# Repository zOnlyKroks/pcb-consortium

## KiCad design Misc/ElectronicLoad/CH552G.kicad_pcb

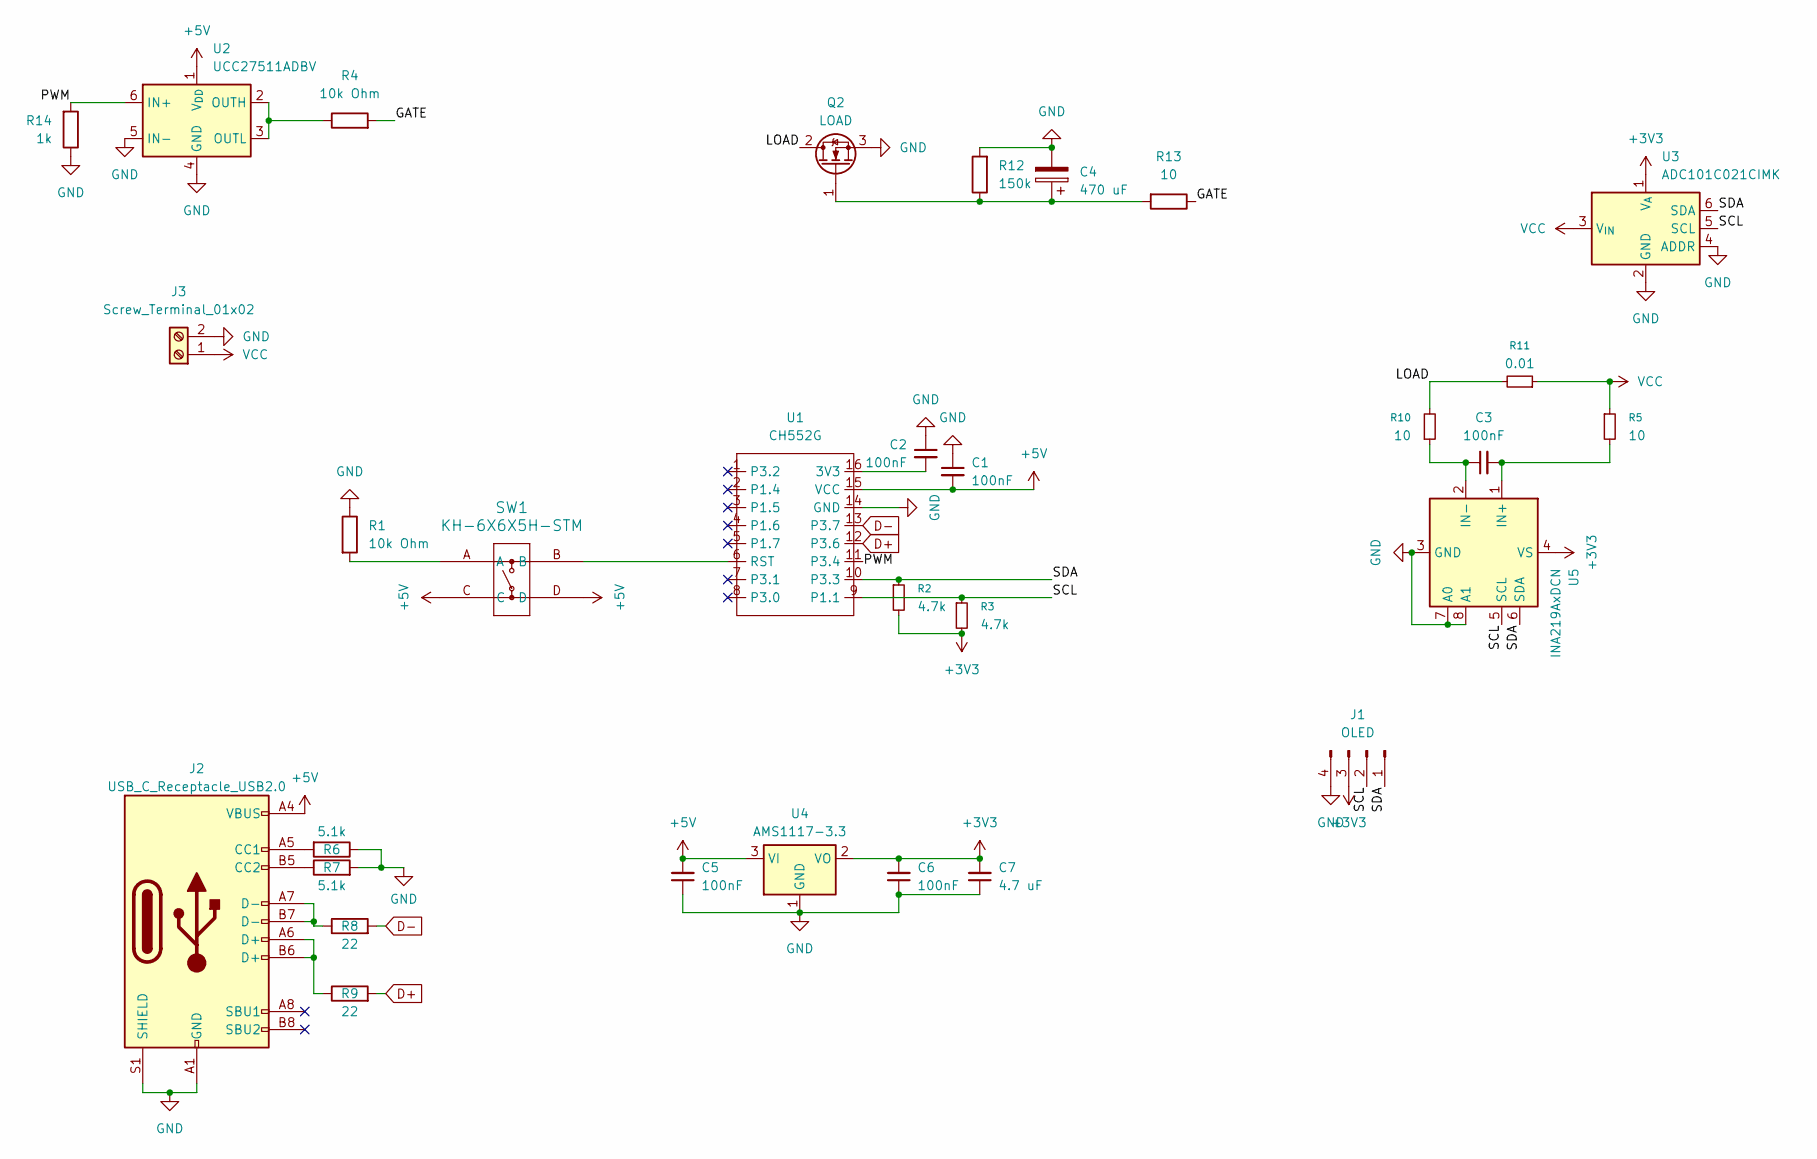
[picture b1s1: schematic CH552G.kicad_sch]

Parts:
C1, C2, C3, C5, C6: 100nF; C_0805_2012Metric; LCSC Part # C49678
C4: 470 uF
C7: 4.7 uF; C_0805_2012Metric; LCSC Part # C49678
J1: OLED; PinHeader_1x04_P2.54mm_Vertical
J2: USB_C_Receptacle_USB2.0; USB_C_Receptacle_HRO_TYPE-C-31-M-12; JlcRotOffset 180
J3: Screw_Terminal_01x02; WJ500V-5.08-2P
Q2: LOAD; TO-220-3_Vertical
R1, R4: 10k Ohm; R_0805_2012Metric; LCSC Part # C17414
R2, R3: 4.7k; R_0805_2012Metric
R5, R10: 10; R_0805_2012Metric
R6, R7: 5.1k; R_0805_2012Metric; LCSC Part # C23186
R8, R9: 22; R_0805_2012Metric; LCSC Part # C23345
R11: 0.01; R_0805_2012Metric
R12: 150k; R_0805_2012Metric; LCSC Part # C17414
R13: 10; R_0805_2012Metric; LCSC Part # C17414
R14: 1k; R_0805_2012Metric; LCSC Part # C17414
SW1: KH-6X6X5H-STM; KH-6X6X5H-STM_SKE; LCSC Part # C2837531
U1: CH552G; LCSC Part # C111292
U2: UCC27511ADBV; SOT-23-6
U3: ADC101C021CIMK; SOT-23-6
U4: AMS1117-3.3; SOT-223-3_TabPin2
U5: INA219AxDCN; SOT-23-8

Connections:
+3V3: C6.2, C7.2, J1.3, R2.2, R3.2, U3.1 (V_{A}), U4.2 (VO), U5.4 (VS)
+5V: C1.2, C5.2, J2.A4 (VBUS), J2.A9 (VBUS), J2.B4 (VBUS), J2.B9 (VBUS), SW1.C, SW1.D, U1.15 (VCC), U2.1 (V_{DD}), U4.3 (VI)
/GATE: R4.2, R13.1
/LOAD: Q2.2 (D), R10.2, R11.2
/PWM: R14.2, U1.11 (P3.4), U2.6 (IN+)
/SCL: J1.2, R3.1, U1.9 (P1.1), U3.5 (SCL), U5.5 (SCL)
/SDA: J1.1, R2.1, U1.10 (P3.3), U3.6 (SDA), U5.6 (SDA)
D+: R9.2, U1.12 (P3.6)
D-: R8.2, U1.13 (P3.7)
GND: C1.1, C2.1, C4.2, C5.1, C6.1, C7.1, J1.4, J2.A1 (GND), J2.A12 (GND), J2.B1 (GND), J2.B12 (GND), J2.S1 (SHIELD), J3.2, Q2.3 (S), R1.1, R6.1, R7.2, R12.2, R14.1, U1.14 (GND), U2.4 (GND), U2.5 (IN-), U3.2 (GND), U3.4 (ADDR), U4.1 (GND), U5.3 (GND), U5.7 (A0), U5.8 (A1)
unnamed: J2.A5 (CC1), R6.2
unnamed: J2.B5 (CC2), R7.1
unnamed: J2.A6 (D+), J2.B6 (D+), R9.1
unnamed: J2.A7 (D-), J2.B7 (D-), R8.1
unnamed: C4.1, Q2.1 (G), R12.1, R13.2
unnamed: R1.2, SW1.A
unnamed: C2.2, U1.16 (3V3)
unnamed: SW1.B, U1.6 (RST)
unnamed: R4.1, U2.2 (OUTH), U2.3 (OUTL)
unnamed: C3.2, R5.2, U5.1 (IN+)
unnamed: C3.1, R10.1, U5.2 (IN-)
VCC: J3.1, R5.1, R11.1, U3.3 (V_{IN})

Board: 2 copper layers, 31 parts (0 on the bottom side), 22 nets, no tracks yet.

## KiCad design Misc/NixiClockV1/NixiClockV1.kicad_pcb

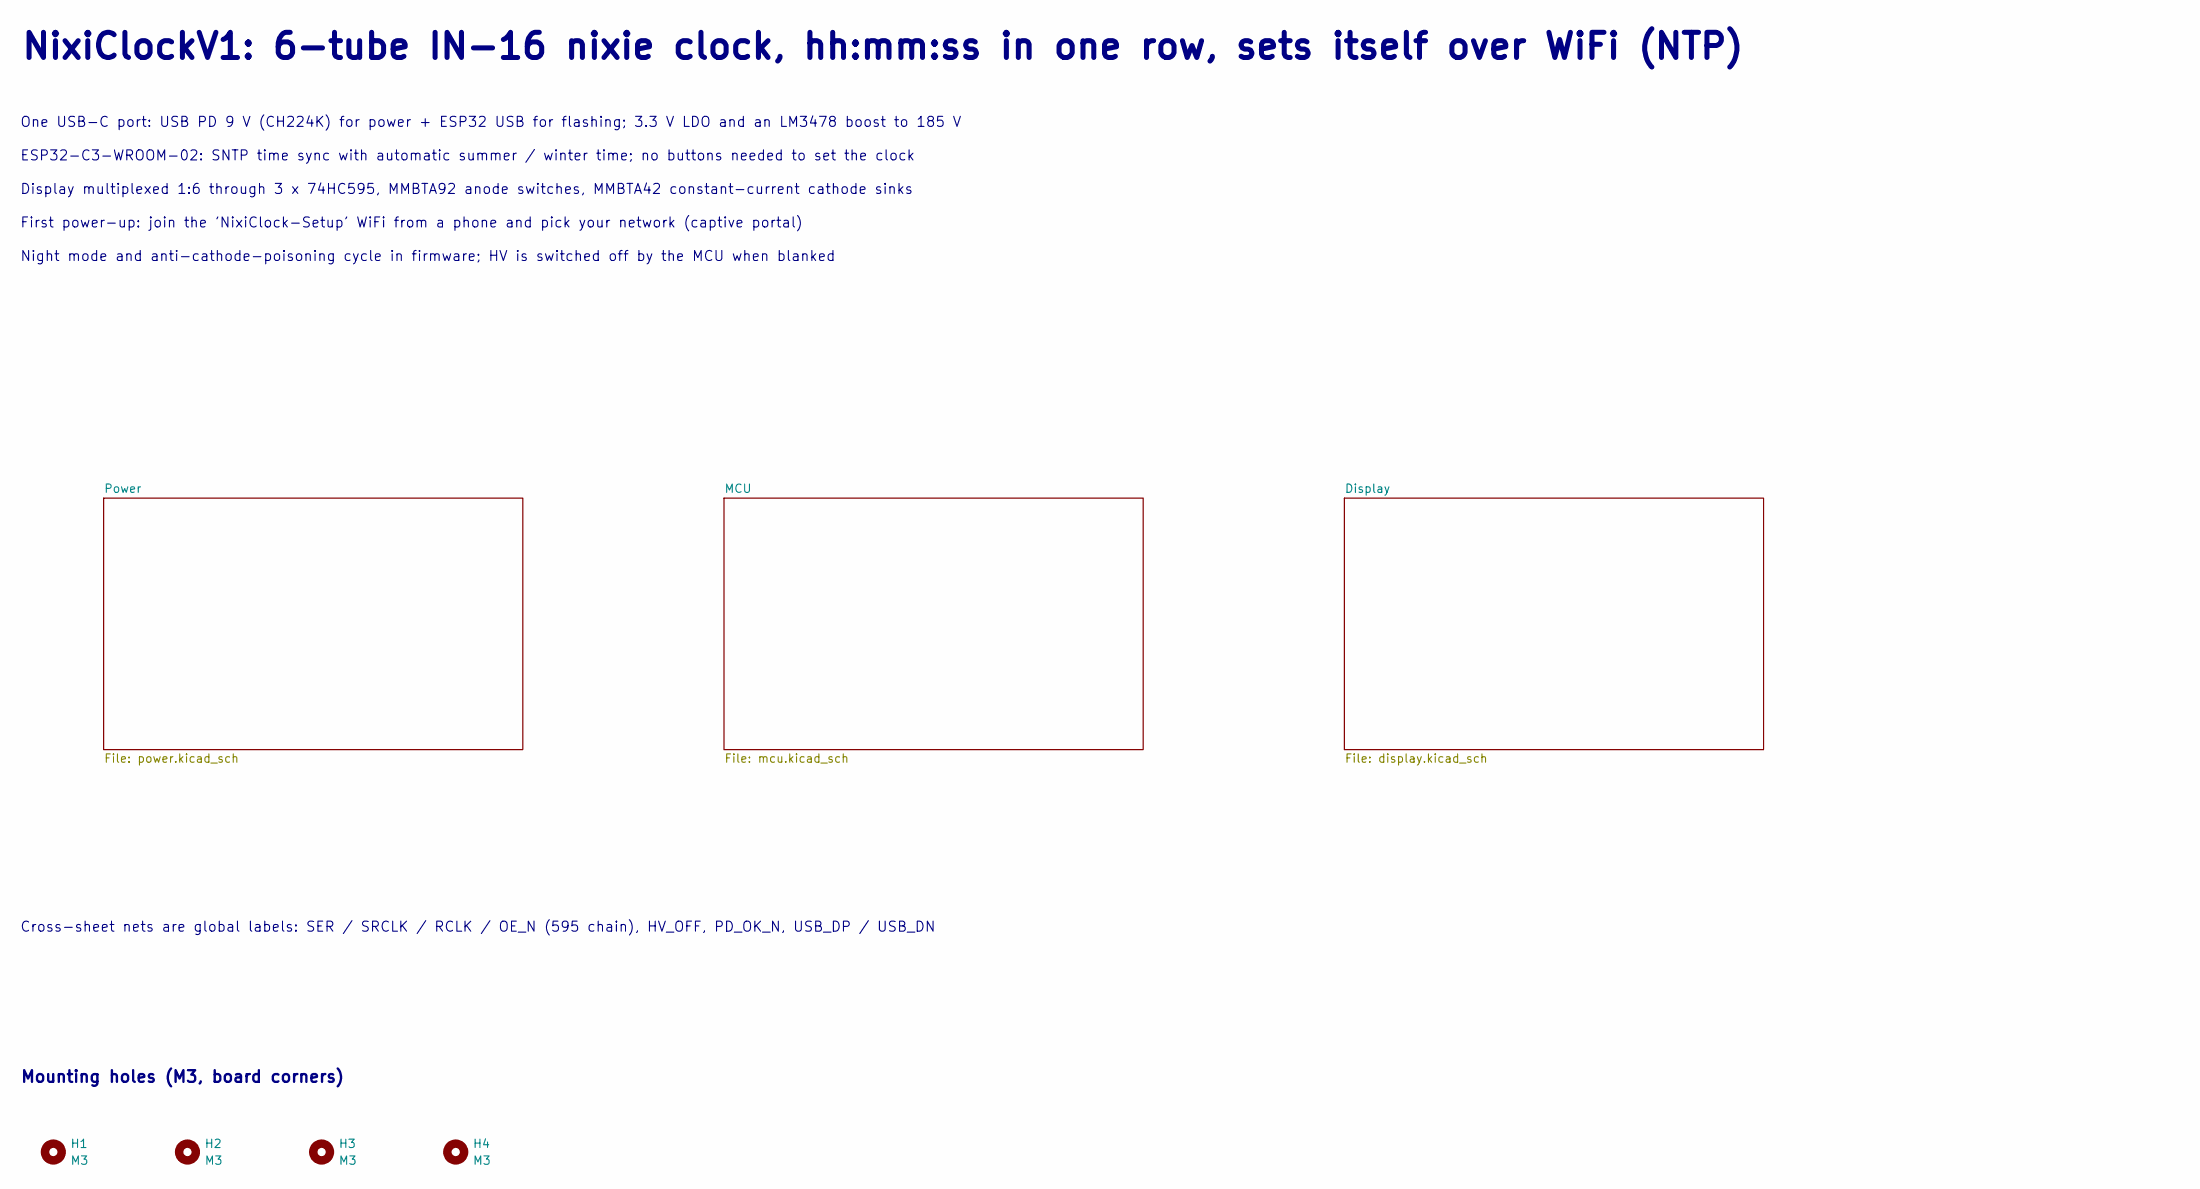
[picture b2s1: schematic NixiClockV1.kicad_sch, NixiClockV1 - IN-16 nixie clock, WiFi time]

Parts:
H1, H2, H3, H4: M3; MountingHole_3.2mm_M3

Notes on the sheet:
Night mode and anti-cathode-poisoning cycle in firmware; HV is switched off by the MCU when blanked
Mounting holes (M3, board corners)
Display multiplexed 1:6 through 3 x 74HC595, MMBTA92 anode switches, MMBTA42 constant-current cathode sinks
Cross-sheet nets are global labels: SER / SRCLK / RCLK / OE_N (595 chain), HV_OFF, PD_OK_N, USB_DP / USB_DN
One USB-C port: USB PD 9 V (CH224K) for power + ESP32 USB for flashing; 3.3 V LDO and an LM3478 boost to 185 V
First power-up: join the 'NixiClock-Setup' WiFi from a phone and pick your network (captive portal)
ESP32-C3-WROOM-02: SNTP time sync with automatic summer / winter time; no buttons needed to set the clock
NixiClockV1: 6-tube IN-16 nixie clock, hh:mm:ss in one row, sets itself over WiFi (NTP)

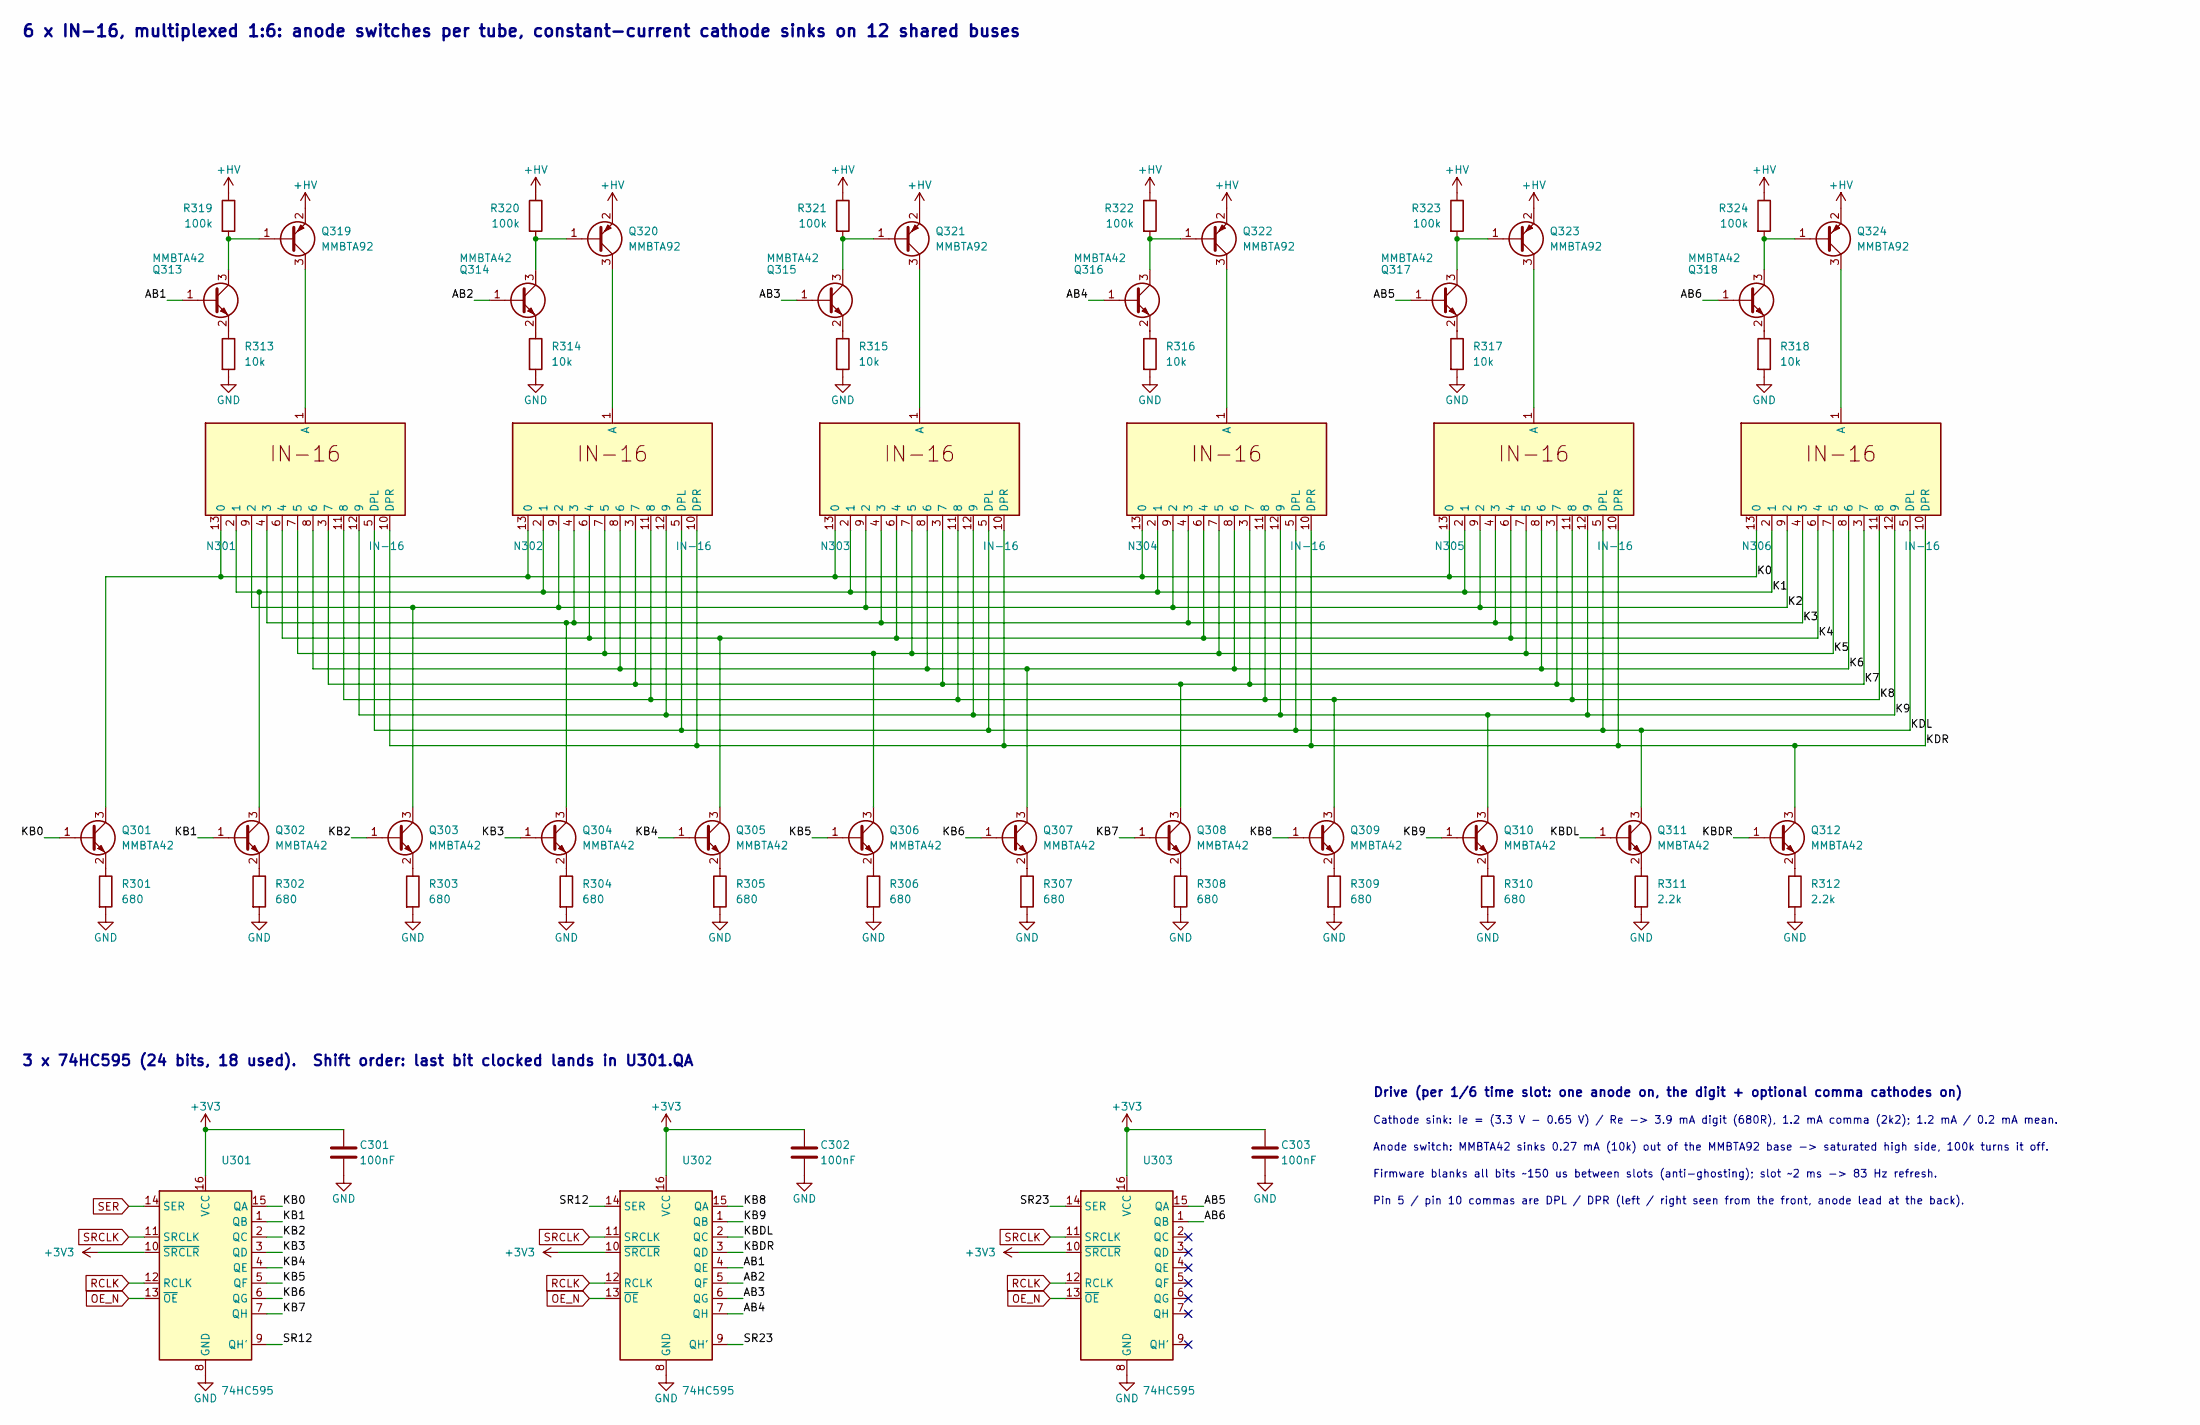
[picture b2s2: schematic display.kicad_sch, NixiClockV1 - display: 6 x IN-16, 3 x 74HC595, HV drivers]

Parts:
C301, C302, C303: 100nF; C_0603_1608Metric; LCSC Part # C14663
N301, N302, N303, N304, N305, N306: IN-16
Q301, Q302, Q303, Q304, Q305, Q306, Q307, Q308, Q309, Q310, Q311, Q312, Q313, Q314, Q315, Q316, Q317, Q318: MMBTA42; SOT-23; LCSC Part # C20069138
Q319, Q320, Q321, Q322, Q323, Q324: MMBTA92; SOT-23; LCSC Part # C20069146
R301, R302, R303, R304, R305, R306, R307, R308, R309, R310: 680; R_0603_1608Metric; LCSC Part # C23228
R311, R312: 2.2k; R_0603_1608Metric; LCSC Part # C4190
R313, R314, R315, R316, R317, R318: 10k; R_0603_1608Metric; LCSC Part # C25804
R319, R320, R321, R322, R323, R324: 100k; R_0603_1608Metric; LCSC Part # C25803
U301, U302, U303: 74HC595; SOIC-16_3.9x9.9mm_P1.27mm; LCSC Part # C20612517

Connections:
+3V3: C301.1, C302.1, C303.1, U301.10 (~SRCLR), U301.16 (VCC), U302.10 (~SRCLR), U302.16 (VCC), U303.10 (~SRCLR), U303.16 (VCC); also elsewhere on the board
+HV: Q319.2 (E), Q320.2 (E), Q321.2 (E), Q322.2 (E), Q323.2 (E), Q324.2 (E), R319.1, R320.1, R321.1, R322.1, R323.1, R324.1; also elsewhere on the board
/Display/AB1: Q313.1 (B), U302.4 (QE)
/Display/AB2: Q314.1 (B), U302.5 (QF)
/Display/AB3: Q315.1 (B), U302.6 (QG)
/Display/AB4: Q316.1 (B), U302.7 (QH)
/Display/AB5: Q317.1 (B), U303.15 (QA)
/Display/AB6: Q318.1 (B), U303.1 (QB)
/Display/K0: N301.13 (0), N302.13 (0), N303.13 (0), N304.13 (0), N305.13 (0), N306.13 (0), Q301.3 (C)
/Display/K1: N301.2 (1), N302.2 (1), N303.2 (1), N304.2 (1), N305.2 (1), N306.2 (1), Q302.3 (C)
/Display/K2: N301.9 (2), N302.9 (2), N303.9 (2), N304.9 (2), N305.9 (2), N306.9 (2), Q303.3 (C)
/Display/K3: N301.4 (3), N302.4 (3), N303.4 (3), N304.4 (3), N305.4 (3), N306.4 (3), Q304.3 (C)
/Display/K4: N301.6 (4), N302.6 (4), N303.6 (4), N304.6 (4), N305.6 (4), N306.6 (4), Q305.3 (C)
/Display/K5: N301.7 (5), N302.7 (5), N303.7 (5), N304.7 (5), N305.7 (5), N306.7 (5), Q306.3 (C)
/Display/K6: N301.8 (6), N302.8 (6), N303.8 (6), N304.8 (6), N305.8 (6), N306.8 (6), Q307.3 (C)
/Display/K7: N301.3 (7), N302.3 (7), N303.3 (7), N304.3 (7), N305.3 (7), N306.3 (7), Q308.3 (C)
/Display/K8: N301.11 (8), N302.11 (8), N303.11 (8), N304.11 (8), N305.11 (8), N306.11 (8), Q309.3 (C)
/Display/K9: N301.12 (9), N302.12 (9), N303.12 (9), N304.12 (9), N305.12 (9), N306.12 (9), Q310.3 (C)
/Display/KB0: Q301.1 (B), U301.15 (QA)
/Display/KB1: Q302.1 (B), U301.1 (QB)
/Display/KB2: Q303.1 (B), U301.2 (QC)
/Display/KB3: Q304.1 (B), U301.3 (QD)
/Display/KB4: Q305.1 (B), U301.4 (QE)
/Display/KB5: Q306.1 (B), U301.5 (QF)
/Display/KB6: Q307.1 (B), U301.6 (QG)
/Display/KB7: Q308.1 (B), U301.7 (QH)
/Display/KB8: Q309.1 (B), U302.15 (QA)
/Display/KB9: Q310.1 (B), U302.1 (QB)
/Display/KBDL: Q311.1 (B), U302.2 (QC)
/Display/KBDR: Q312.1 (B), U302.3 (QD)
/Display/KDL: N301.5 (DPL), N302.5 (DPL), N303.5 (DPL), N304.5 (DPL), N305.5 (DPL), N306.5 (DPL), Q311.3 (C)
/Display/KDR: N301.10 (DPR), N302.10 (DPR), N303.10 (DPR), N304.10 (DPR), N305.10 (DPR), N306.10 (DPR), Q312.3 (C)
/Display/SR12: U301.9 (QH'), U302.14 (SER)
/Display/SR23: U302.9 (QH'), U303.14 (SER)
GND: C301.2, C302.2, C303.2, R301.2, R302.2, R303.2, R304.2, R305.2, R306.2, R307.2, R308.2, R309.2, R310.2, R311.2, R312.2, R313.2, R314.2, R315.2, R316.2, R317.2, R318.2, U301.8 (GND), U302.8 (GND), U303.8 (GND); also elsewhere on the board
unnamed: N301.1 (A), Q319.3 (C)
unnamed: N302.1 (A), Q320.3 (C)
unnamed: N303.1 (A), Q321.3 (C)
unnamed: N304.1 (A), Q322.3 (C)
unnamed: N305.1 (A), Q323.3 (C)
unnamed: N306.1 (A), Q324.3 (C)
unnamed: Q301.2 (E), R301.1
unnamed: Q302.2 (E), R302.1
unnamed: Q303.2 (E), R303.1
unnamed: Q304.2 (E), R304.1
unnamed: Q305.2 (E), R305.1
unnamed: Q306.2 (E), R306.1
unnamed: Q307.2 (E), R307.1
unnamed: Q308.2 (E), R308.1
unnamed: Q309.2 (E), R309.1
unnamed: Q310.2 (E), R310.1
unnamed: Q311.2 (E), R311.1
unnamed: Q312.2 (E), R312.1
unnamed: Q313.3 (C), Q319.1 (B), R319.2
unnamed: Q313.2 (E), R313.1
unnamed: Q314.3 (C), Q320.1 (B), R320.2
unnamed: Q314.2 (E), R314.1
unnamed: Q315.3 (C), Q321.1 (B), R321.2
unnamed: Q315.2 (E), R315.1
unnamed: Q316.3 (C), Q322.1 (B), R322.2
unnamed: Q316.2 (E), R316.1
unnamed: Q317.3 (C), Q323.1 (B), R323.2
unnamed: Q317.2 (E), R317.1
unnamed: Q318.3 (C), Q324.1 (B), R324.2
unnamed: Q318.2 (E), R318.1
OE_N: U301.13 (~OE), U302.13 (~OE), U303.13 (~OE); also elsewhere on the board
RCLK: U301.12 (RCLK), U302.12 (RCLK), U303.12 (RCLK); also elsewhere on the board
SER: U301.14 (SER); also elsewhere on the board
SRCLK: U301.11 (SRCLK), U302.11 (SRCLK), U303.11 (SRCLK); also elsewhere on the board

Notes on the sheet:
3 x 74HC595 (24 bits, 18 used). Shift order: last bit clocked lands in U301.QA
Drive (per 1/6 time slot: one anode on, the digit + optional comma cathodes on)
Pin 5 / pin 10 commas are DPL / DPR (left / right seen from the front, anode lead at the back).
6 x IN-16, multiplexed 1:6: anode switches per tube, constant-current cathode sinks on 12 shared buses
Firmware blanks all bits ~150 us between slots (anti-ghosting); slot ~2 ms -> 83 Hz refresh.
Anode switch: MMBTA42 sinks 0.27 mA (10k) out of the MMBTA92 base -> saturated high side, 100k turns it off.
Cathode sink: Ie = (3.3 V - 0.65 V) / Re -> 3.9 mA digit (680R), 1.2 mA comma (2k2); 1.2 mA / 0.2 mA mean.

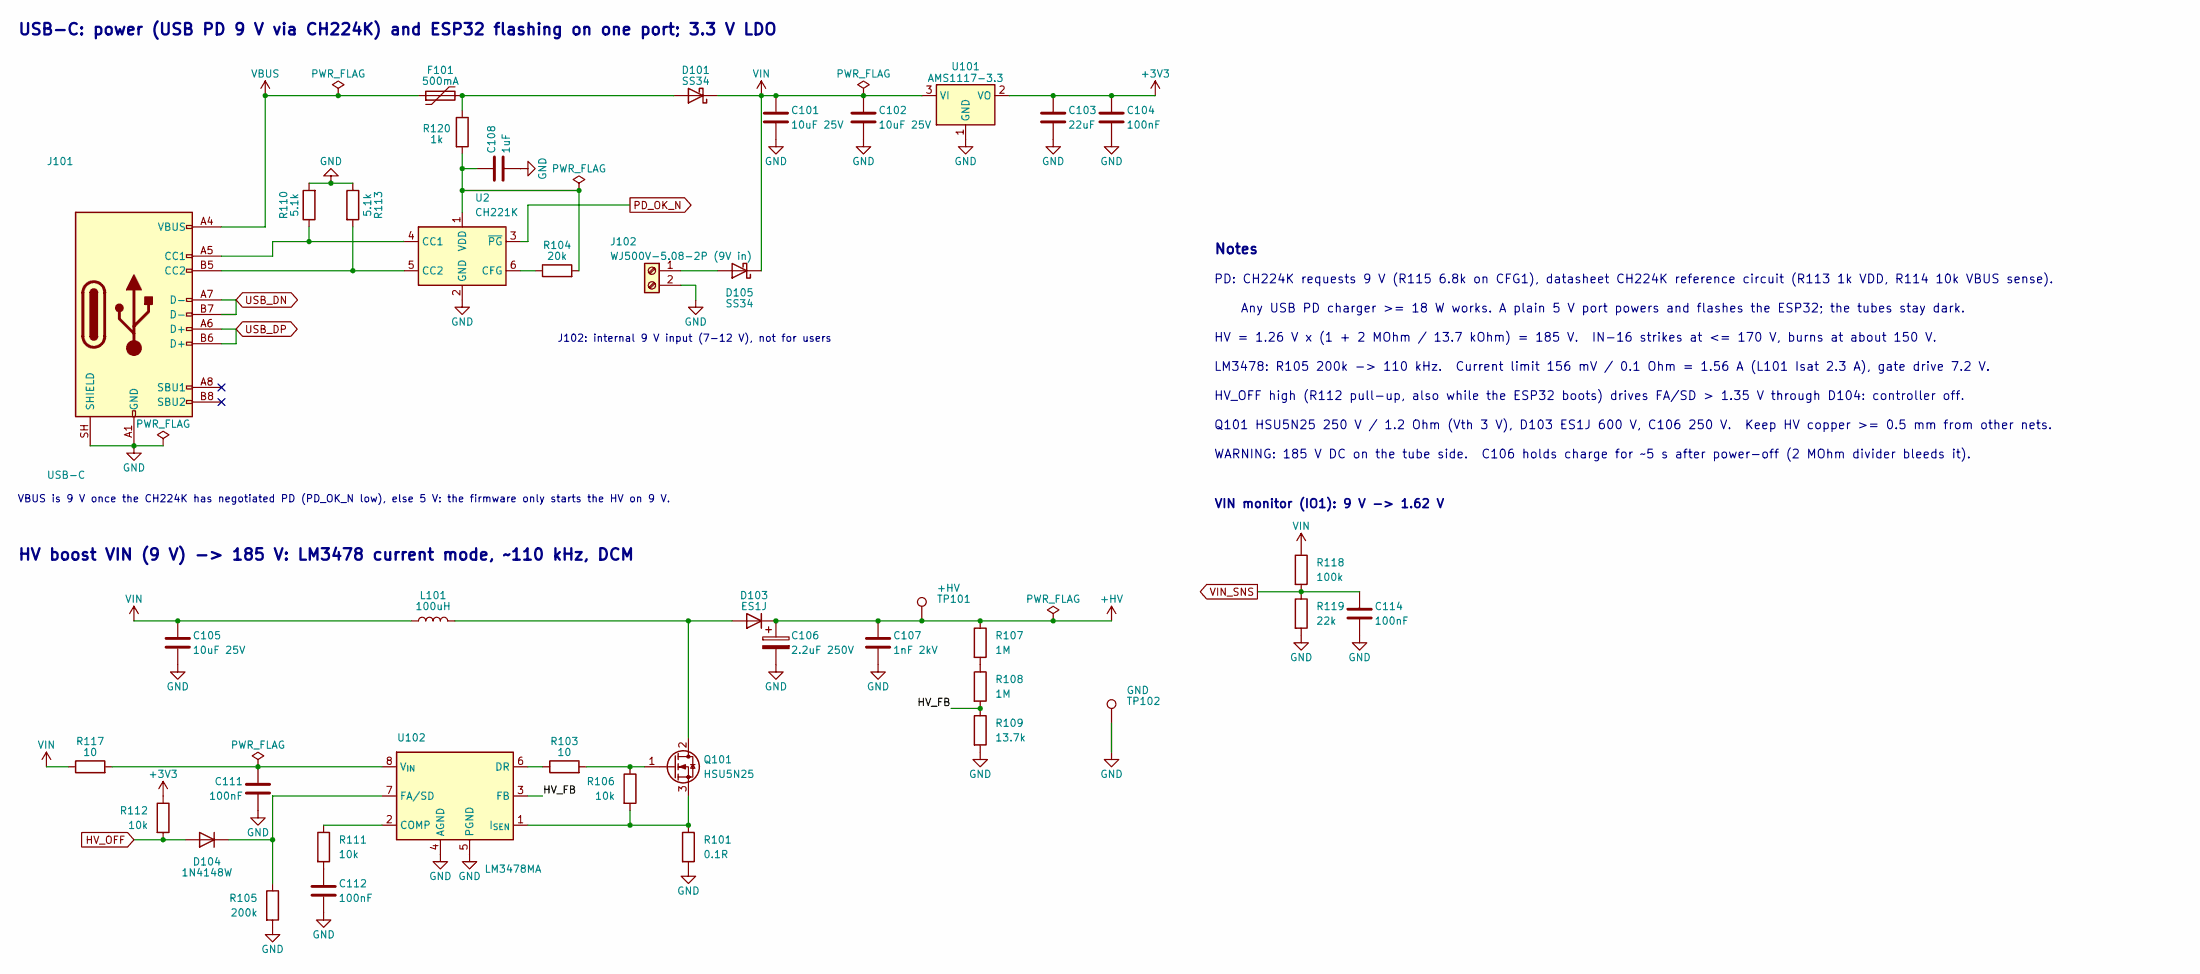
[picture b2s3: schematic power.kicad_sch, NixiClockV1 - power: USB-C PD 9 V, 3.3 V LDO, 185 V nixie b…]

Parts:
C101, C102, C105: 10uF 25V; C_0805_2012Metric; LCSC Part # C15850
C103: 22uF; C_0805_2012Metric; LCSC Part # C45783
C104, C111, C112, C114: 100nF; C_0603_1608Metric; LCSC Part # C14663
C106: 2.2uF 250V; CP_Elec_6.3x9.9; LCSC Part # C22387991
C107: 1nF 2kV; C_1206_3216Metric; LCSC Part # C9196
C108: 1uF; C_0603_1608Metric; LCSC Part # C15849
D101, D105: SS34; D_SMA; LCSC Part # C8678
D103: ES1J; D_SMA; LCSC Part # C18199159
D104: 1N4148W; D_SOD-123; LCSC Part # C81598
F101: 500mA; Fuse_1206_3216Metric; LCSC Part # C135341
J101: USB-C; USB_C_Receptacle_HRO_TYPE-C-31-M-12; LCSC Part # C165948
J102: WJ500V-5.08-2P (9V in); TerminalBlock_Phoenix_MKDS-1,5-2-5.08_1x02_P5.08mm_Horizont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; LCSC Part # C8465
L101: 100uH; L_APV_APH1040; LCSC Part # C19634020
Q101: HSU5N25; TO-252-2; LCSC Part # C22359255
R101: 0.1R; R_1206_3216Metric; LCSC Part # C25334
R103, R117: 10; R_0603_1608Metric; LCSC Part # C22859
R104: 20k; R_0603_1608Metric; LCSC Part # C4184
R105: 200k; R_0603_1608Metric; LCSC Part # C25811
R106, R111, R112: 10k; R_0603_1608Metric; LCSC Part # C25804
R107, R108: 1M; R_1206_3216Metric; LCSC Part # C17927
R109: 13.7k; R_0603_1608Metric; LCSC Part # C407628
R110, R113: 5.1k; R_0603_1608Metric; LCSC Part # C23186
R118: 100k; R_0603_1608Metric; LCSC Part # C25803
R119: 22k; R_0603_1608Metric; LCSC Part # C31850
R120: 1k; R_0603_1608Metric; LCSC Part # C21190
TP101: +HV; TestPoint_Pad_D1.5mm
TP102: GND; TestPoint_Pad_D1.5mm
U2: CH221K; SOT-23-6; LCSC Part # C5125736
U101: AMS1117-3.3; SOT-223-3_TabPin2; LCSC Part # C6186
U102: LM3478MA; SOIC-8_3.9x4.9mm_P1.27mm; LCSC Part # C115907

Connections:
+3V3: C103.1, C104.1, R112.1, U101.2 (VO); also elsewhere on the board
+HV: C106.1, C107.1, D103.1 (K), R107.1, TP101.1 (1_1); also elsewhere on the board
/Power/HV_FB: R108.2, R109.1, U102.3 (FB)
GND: C101.2, C102.2, C103.2, C104.2, C105.2, C106.2, C107.2, C108.2, C111.2, C112.2, C114.2, J101.A1 (GND), J101.A12 (GND), J101.B1 (GND), J101.B12 (GND), J101.SH (SHIELD), J102.2, R101.2, R105.2, R109.2, R110.2, R113.1, R119.2, TP102.1 (1_1), U2.2 (GND), U101.1 (GND), U102.4 (AGND), U102.5 (PGND); also elsewhere on the board
HV_OFF: D104.2 (A), R112.2; also elsewhere on the board
unnamed: C112.1, R111.2
unnamed: D101.2 (A), F101.2, R120.1
unnamed: D103.2 (A), L101.2, Q101.2 (D)
unnamed: D104.1 (K), R105.1, U102.7 (FA/SD)
unnamed: D105.2 (A), J102.1
unnamed: J101.A5 (CC1), R110.1, U2.4 (CC1)
unnamed: J101.B5 (CC2), R113.2, U2.5 (CC2)
unnamed: Q101.1 (G), R103.2, R106.1
unnamed: Q101.3 (S), R101.1, R106.2, U102.1 (I_{SEN})
unnamed: R107.2, R108.1
unnamed: R104.1, U2.6 (CFG)
unnamed: C108.1, R104.2, R120.2, U2.1 (VDD)
unnamed: R111.1, U102.2 (COMP)
unnamed: R103.1, U102.6 (DR)
unnamed: C111.1, R117.2, U102.8 (V_{IN})
PD_OK_N: U2.3 (~PG); also elsewhere on the board
USB_DN: J101.A7 (D-), J101.B7 (D-); also elsewhere on the board
USB_DP: J101.A6 (D+), J101.B6 (D+); also elsewhere on the board
VBUS: F101.1, J101.A4 (VBUS), J101.A9 (VBUS), J101.B4 (VBUS), J101.B9 (VBUS)
VIN: C101.1, C102.1, C105.1, D101.1 (K), D105.1 (K), L101.1, R117.1, R118.1, U101.3 (VI)
VIN_SNS: C114.1, R118.2, R119.1; also elsewhere on the board

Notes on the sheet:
PD: CH224K requests 9 V (R115 6.8k on CFG1), datasheet CH224K reference circuit (R113 1k VDD, R114 10k VBUS sense).
HV_OFF high (R112 pull-up, also while the ESP32 boots) drives FA/SD > 1.35 V through D104: controller off.
Notes
HV = 1.26 V x (1 + 2 MOhm / 13.7 kOhm) = 185 V. IN-16 strikes at <= 170 V, burns at about 150 V.
Any USB PD charger >= 18 W works. A plain 5 V port powers and flashes the ESP32; the tubes stay dark.
USB-C: power (USB PD 9 V via CH224K) and ESP32 flashing on one port; 3.3 V LDO
WARNING: 185 V DC on the tube side. C106 holds charge for ~5 s after power-off (2 MOhm divider bleeds it).
J102: internal 9 V input (7-12 V), not for users
HV boost VIN (9 V) -> 185 V: LM3478 current mode, ~110 kHz, DCM
Q101 HSU5N25 250 V / 1.2 Ohm (Vth 3 V), D103 ES1J 600 V, C106 250 V. Keep HV copper >= 0.5 mm from other nets.
VIN monitor (IO1): 9 V -> 1.62 V
VBUS is 9 V once the CH224K has negotiated PD (PD_OK_N low), else 5 V: the firmware only starts the HV on 9 V.
LM3478: R105 200k -> 110 kHz. Current limit 156 mV / 0.1 Ohm = 1.56 A (L101 Isat 2.3 A), gate drive 7.2 V.

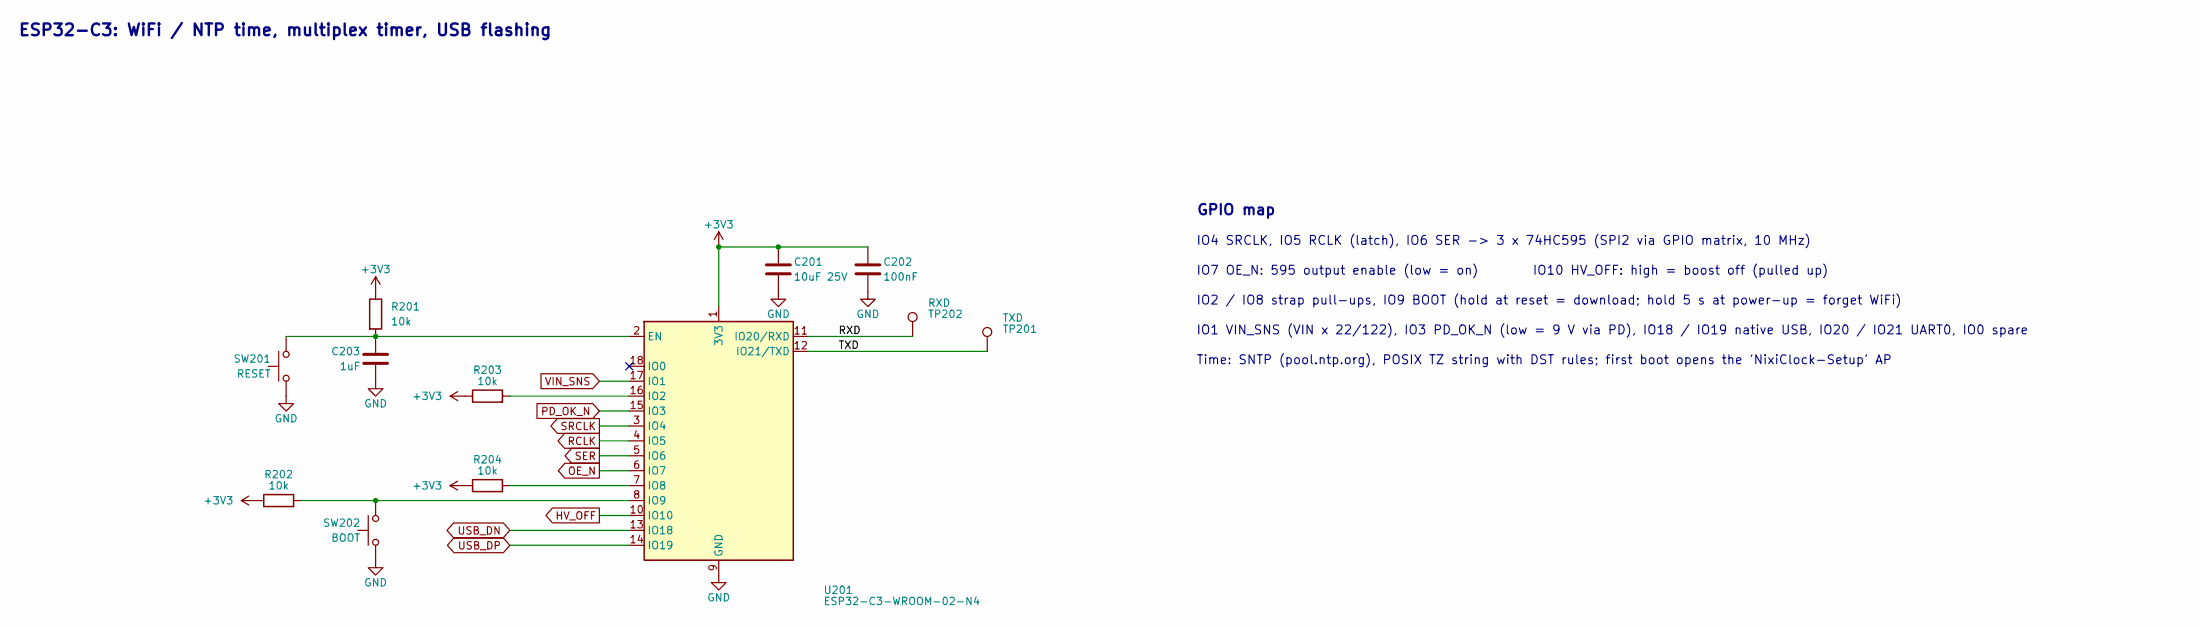
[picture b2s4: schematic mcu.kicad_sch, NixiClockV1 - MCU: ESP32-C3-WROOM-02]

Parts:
C201: 10uF 25V; C_0805_2012Metric; LCSC Part # C15850
C202: 100nF; C_0603_1608Metric; LCSC Part # C14663
C203: 1uF; C_0603_1608Metric; LCSC Part # C15849
R201, R202, R203, R204: 10k; R_0603_1608Metric; LCSC Part # C25804
SW201: RESET; SW-SMD_4P-L5.1-W5.1-P3.70-LS6.5-TL_H1.5; LCSC Part # C318884
SW202: BOOT; SW-SMD_4P-L5.1-W5.1-P3.70-LS6.5-TL_H1.5; LCSC Part # C318884
TP201: TXD; TestPoint_Pad_D1.5mm
TP202: RXD; TestPoint_Pad_D1.5mm
U201: ESP32-C3-WROOM-02-N4; ESP32-C3-WROOM-02; LCSC Part # C2934560

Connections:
+3V3: C201.1, C202.1, R201.1, R202.1, R203.1, R204.1, U201.1 (3V3); also elsewhere on the board
/MCU/RXD: TP202.1 (1_1), U201.11 (IO20/RXD)
/MCU/TXD: TP201.1 (1_1), U201.12 (IO21/TXD)
GND: C201.2, C202.2, C203.2, SW201.1, SW201.2 (1), SW202.1, SW202.2 (1), U201.9 (GND), U201.19 (GND); also elsewhere on the board
HV_OFF: U201.10 (IO10); also elsewhere on the board
unnamed: C203.1, R201.2, SW201.3 (2), SW201.4 (2), U201.2 (EN)
unnamed: R203.2, U201.16 (IO2)
unnamed: R204.2, U201.7 (IO8)
unnamed: R202.2, SW202.3 (2), SW202.4 (2), U201.8 (IO9)
OE_N: U201.6 (IO7); also elsewhere on the board
PD_OK_N: U201.15 (IO3); also elsewhere on the board
RCLK: U201.4 (IO5); also elsewhere on the board
SER: U201.5 (IO6); also elsewhere on the board
SRCLK: U201.3 (IO4); also elsewhere on the board
USB_DN: U201.13 (IO18); also elsewhere on the board
USB_DP: U201.14 (IO19); also elsewhere on the board
VIN_SNS: U201.17 (IO1); also elsewhere on the board

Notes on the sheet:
IO4 SRCLK, IO5 RCLK (latch), IO6 SER -> 3 x 74HC595 (SPI2 via GPIO matrix, 10 MHz)
GPIO map
Time: SNTP (pool.ntp.org), POSIX TZ string with DST rules; first boot opens the 'NixiClock-Setup' AP
IO2 / IO8 strap pull-ups, IO9 BOOT (hold at reset = download; hold 5 s at power-up = forget WiFi)
IO7 OE_N: 595 output enable (low = on) IO10 HV_OFF: high = boost off (pulled up)
IO1 VIN_SNS (VIN x 22/122), IO3 PD_OK_N (low = 9 V via PD), IO18 / IO19 native USB, IO20 / IO21 UART0, IO0 spare
ESP32-C3: WiFi / NTP time, multiplex timer, USB flashing

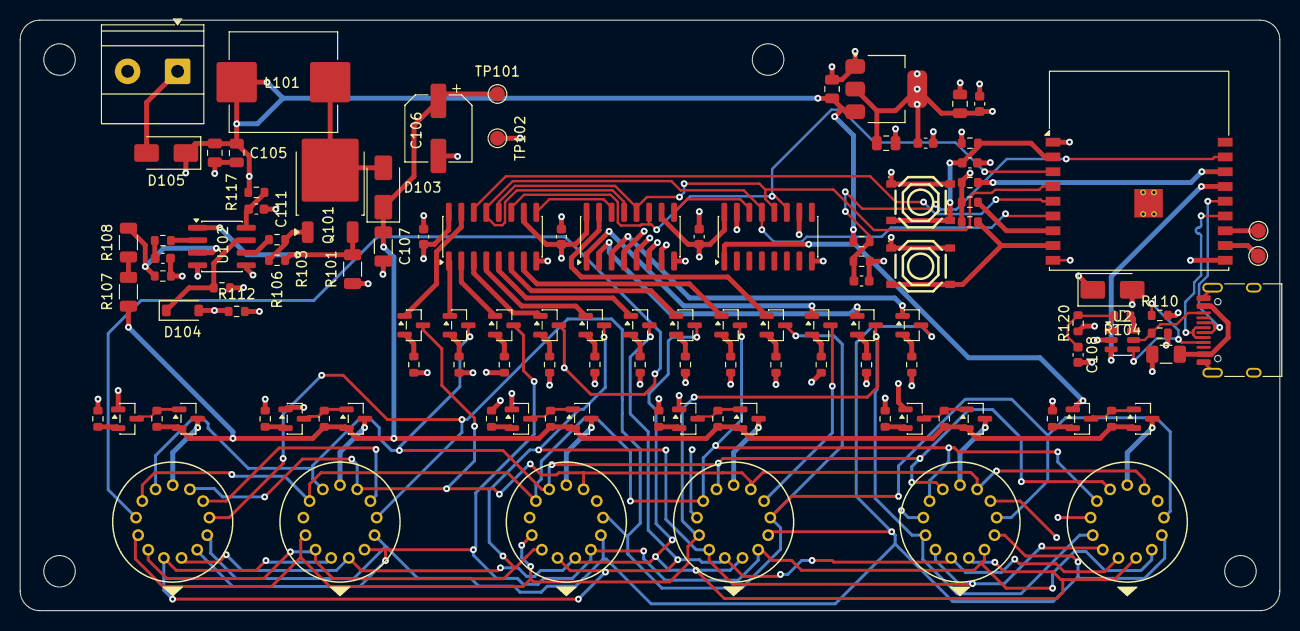
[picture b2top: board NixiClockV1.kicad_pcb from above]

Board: 4 copper layers, 128.0 x 60.0 mm, 117 parts (0 on the bottom side), 98 nets.

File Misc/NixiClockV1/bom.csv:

"Refs","Value","Footprint","LCSC","Qty"
"C101,C102,C105,C201","10uF 25V","Capacitor_SMD:C_0805_2012Metric","C15850","4"
"C103","22uF","Capacitor_SMD:C_0805_2012Metric","C45783","1"
"C104,C111,C112,C114,C202,C301-C303","100nF","Capacitor_SMD:C_0603_1608Metric","C14663","8"
"C106","2.2uF 250V","Capacitor_SMD:CP_Elec_6.3x9.9","C22387991","1"
"C107","1nF 2kV","Capacitor_SMD:C_1206_3216Metric","C9196","1"
"C113,C203","1uF","Capacitor_SMD:C_0603_1608Metric","C15849","2"
"D101,D105","SS34","Diode_SMD:D_SMA","C8678","2"
"D103","ES1J","Diode_SMD:D_SMA","C18199159","1"
"D104","1N4148W","Diode_SMD:D_SOD-123","C81598","1"
"F101","500mA","Fuse:Fuse_1206_3216Metric","C135341","1"
"J101","USB-C","Connector_USB:USB_C_Receptacle_HRO_TYPE-C-31-M-12","C165948","1"
"J102","WJ500V-5.08-2P (9V in)","TerminalBlock_Phoenix:TerminalBlock_Phoenix_MKDS-1,5-2-5.08_1x02_P5.08mm_Horizontal","C8465","1"
"L101","100uH","Inductor_SMD:L_APV_APH1040","C19634020","1"
"N301-N306","IN-16","NixiClockV1:IN-16","","6"
"Q101","HSU5N25","Package_TO_SOT_SMD:TO-252-2","C22359255","1"
"Q301-Q318","MMBTA42","Package_TO_SOT_SMD:SOT-23","C20069138","18"
"Q319-Q324","MMBTA92","Package_TO_SOT_SMD:SOT-23","C20069146","6"
"R101","0.1R","Resistor_SMD:R_1206_3216Metric","C25334","1"
"R103,R117","10","Resistor_SMD:R_0603_1608Metric","C22859","2"
"R105","200k","Resistor_SMD:R_0603_1608Metric","C25811","1"
"R106,R111,R112,R114,R116,R201-R204,R313-R318","10k","Resistor_SMD:R_0603_1608Metric","C25804","15"
"R107,R108","1M","Resistor_SMD:R_1206_3216Metric","C17927","2"
"R109","13.7k","Resistor_SMD:R_0603_1608Metric","C407628","1"
"R113","1k","Resistor_SMD:R_0603_1608Metric","C21190","1"
"R115","6.8k","Resistor_SMD:R_0603_1608Metric","C23212","1"
"R118,R319-R324","100k","Resistor_SMD:R_0603_1608Metric","C25803","7"
"R119","22k","Resistor_SMD:R_0603_1608Metric","C31850","1"
"R301-R310","680","Resistor_SMD:R_0603_1608Metric","C23228","10"
"R311,R312","2.2k","Resistor_SMD:R_0603_1608Metric","C4190","2"
"SW201","RESET","NixiClockV1:SW-SMD_4P-L5.1-W5.1-P3.70-LS6.5-TL_H1.5","C318884","1"
"SW202","BOOT","NixiClockV1:SW-SMD_4P-L5.1-W5.1-P3.70-LS6.5-TL_H1.5","C318884","1"
"U101","AMS1117-3.3","Package_TO_SOT_SMD:SOT-223-3_TabPin2","C6186","1"
"U102","LM3478MA","Package_SO:SOIC-8_3.9x4.9mm_P1.27mm","C115907","1"
"U103","CH224K","Package_SO:SSOP-10-1EP_3.9x4.9mm_P1mm_EP2.1x3.3mm","C970725","1"
"U201","ESP32-C3-WROOM-02-N4","NixiClockV1:ESP32-C3-WROOM-02","C2934560","1"
"U301-U303","74HC595","Package_SO:SOIC-16_3.9x9.9mm_P1.27mm","C20612517","3"
